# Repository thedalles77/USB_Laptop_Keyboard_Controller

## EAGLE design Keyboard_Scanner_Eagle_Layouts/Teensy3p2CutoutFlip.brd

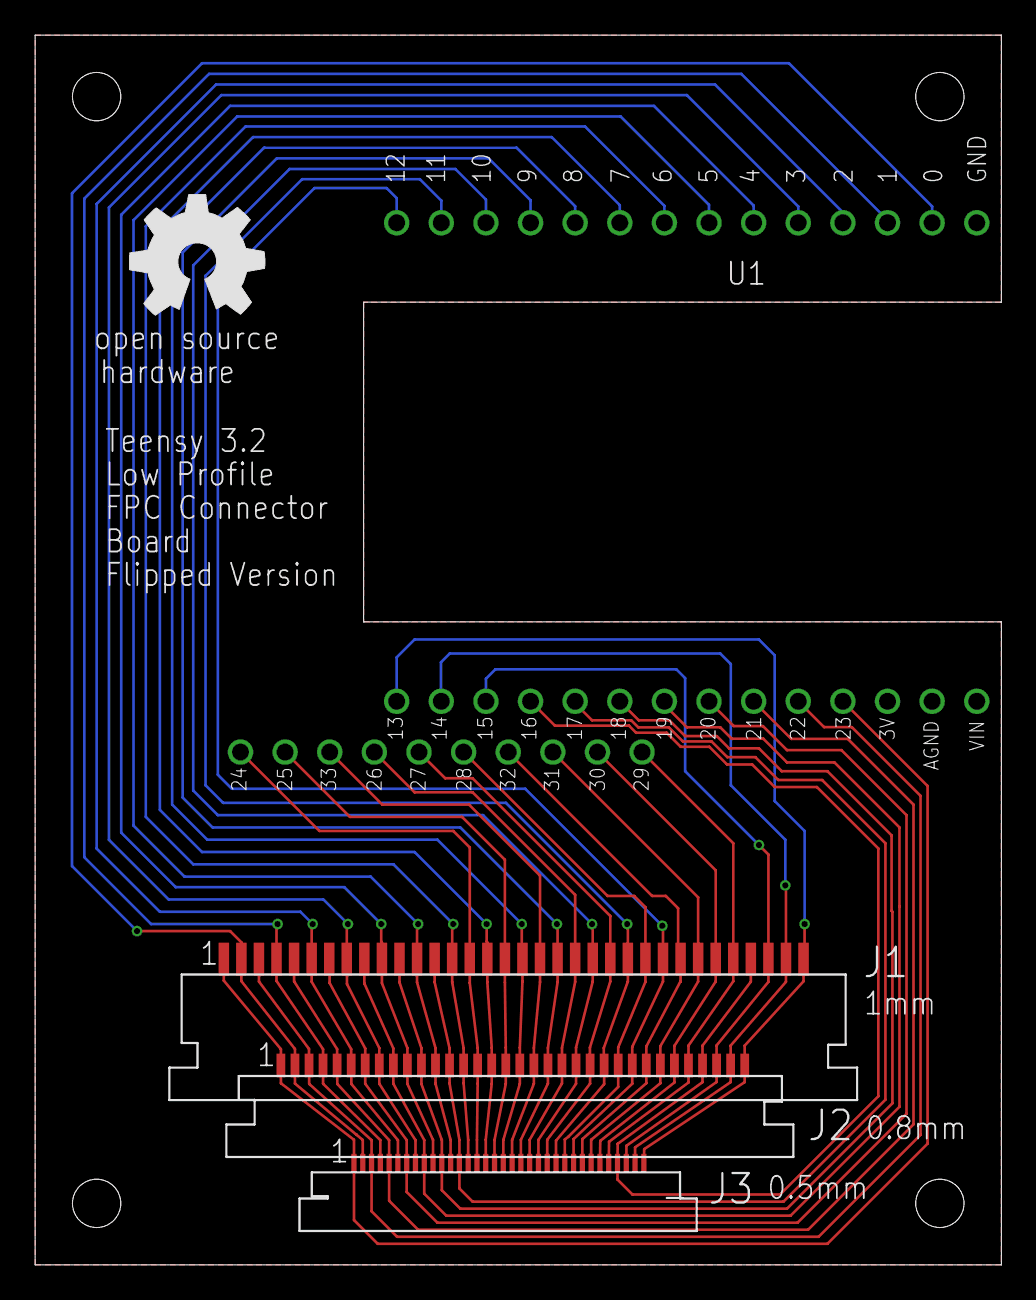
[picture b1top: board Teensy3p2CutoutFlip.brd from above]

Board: 2 copper layers, 55.0 x 70.0 mm, 5 parts (0 on the bottom side), 34 nets.

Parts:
J1: 1mm; FPC34
J2: 0.8mm; FPC34_P8MM
J3: 0.5mm; FPC34_P5MM
U1: Teensy 3.2; TEENSY3P2CUTOUT
U$1: OSHW_8MM

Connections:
0: J1.2, J2.2, J3.2, U1.0
1: J1.4, J2.4, J3.4, U1.1
2: J1.6, J2.6, J3.6, U1.2
3: J1.8, J2.8, J3.8, U1.3
4: J1.10, J2.10, J3.10, U1.4
5: J1.12, J2.12, J3.12, U1.5
6: J1.14, J2.14, J3.14, U1.6
7: J1.16, J2.16, J3.16, U1.7
8: J1.18, J2.18, J3.18, U1.8
9: J1.20, J2.20, J3.20, U1.9
10: J1.22, J2.22, J3.22, U1.10
11: J1.24, J2.24, J3.24, U1.11
12: J1.26, J2.26, J3.26, U1.12
13: J1.34, J2.34, J3.34, U1.13
14: J1.33, J2.33, J3.33, U1.14
15: J1.32, J2.32, J3.32, U1.15
16: J1.31, J2.31, J3.31, U1.16
17: J1.13, J2.13, J3.13, U1.17
18: J1.11, J2.11, J3.11, U1.18
19: J1.9, J2.9, J3.9, U1.19
20: J1.7, J2.7, J3.7, U1.20
21: J1.5, J2.5, J3.5, U1.21
22: J1.3, J2.3, J3.3, U1.22
23: J1.1, J2.1, J3.1, U1.23
24: J1.15, J2.15, J3.15, U1.24
25: J1.17, J2.17, J3.17, U1.25
26: J1.21, J2.21, J3.21, U1.26
27: J1.23, J2.23, J3.23, U1.27
28: J1.25, J2.25, J3.25, U1.28
29: J1.30, J2.30, J3.30, U1.29
30: J1.29, J2.29, J3.29, U1.30
31: J1.28, J2.28, J3.28, U1.31
32: J1.27, J2.27, J3.27, U1.32
33: J1.19, J2.19, J3.19, U1.33

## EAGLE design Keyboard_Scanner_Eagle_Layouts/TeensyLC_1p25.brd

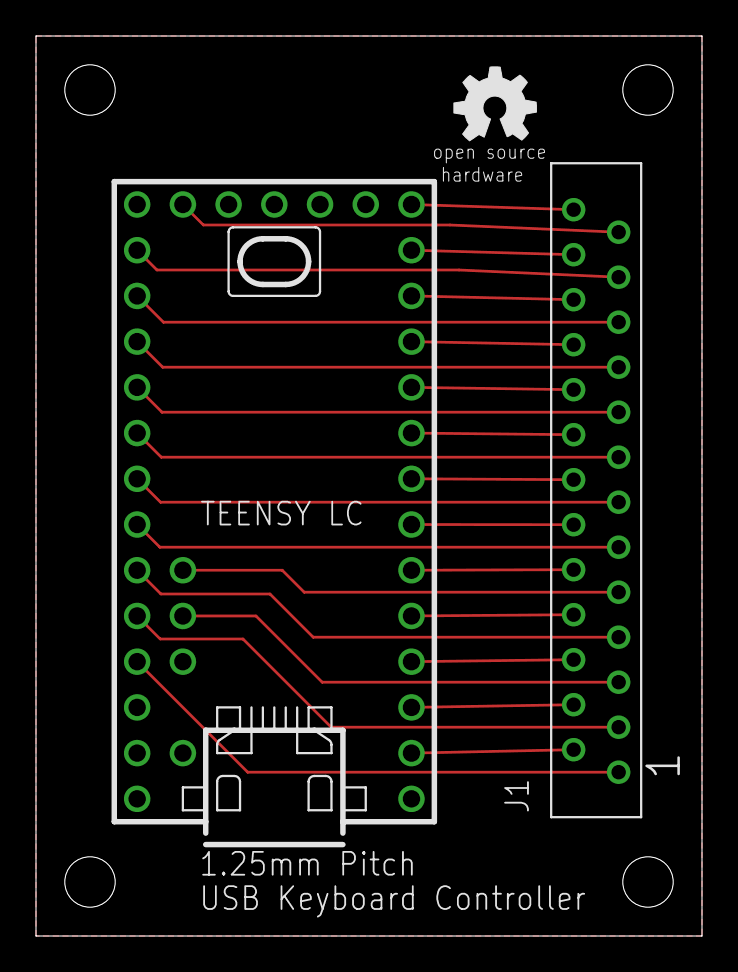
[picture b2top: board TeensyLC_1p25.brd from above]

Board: 2 copper layers, 37.0 x 50.0 mm, 3 parts (0 on the bottom side), 27 nets.

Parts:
J1: 1.25MM DIP FPC; CONN_1P25
U$1: TEENSY_LC
U$2: OSHW_5MM

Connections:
GND: U$1.GND1, U$1.GND2, U$1.GND3
IO_0: J1.P$2, U$1.0
IO_1: J1.P$4, U$1.1
IO_2: J1.P$6, U$1.2
IO_3: J1.P$8, U$1.3
IO_4: J1.P$10, U$1.4
IO_5: J1.P$12, U$1.5
IO_6: J1.P$14, U$1.6
IO_7: J1.P$16, U$1.7
IO_8: J1.P$18, U$1.8
IO_9: J1.P$20, U$1.9
IO_10: J1.P$22, U$1.10
IO_11: J1.P$24, U$1.11
IO_12: J1.P$26, U$1.12
IO_14: J1.P$23, U$1.14
IO_15: J1.P$21, U$1.15
IO_16: J1.P$19, U$1.16
IO_17: J1.P$17, U$1.17
IO_18: J1.P$15, U$1.18
IO_19: J1.P$13, U$1.19
IO_20: J1.P$11, U$1.20
IO_21: J1.P$7, U$1.21
IO_22: J1.P$3, U$1.22
IO_23: J1.P$1, U$1.23
IO_24: J1.P$5, U$1.24
IO_25: J1.P$9, U$1.25
IO_26: J1.P$25, U$1.26

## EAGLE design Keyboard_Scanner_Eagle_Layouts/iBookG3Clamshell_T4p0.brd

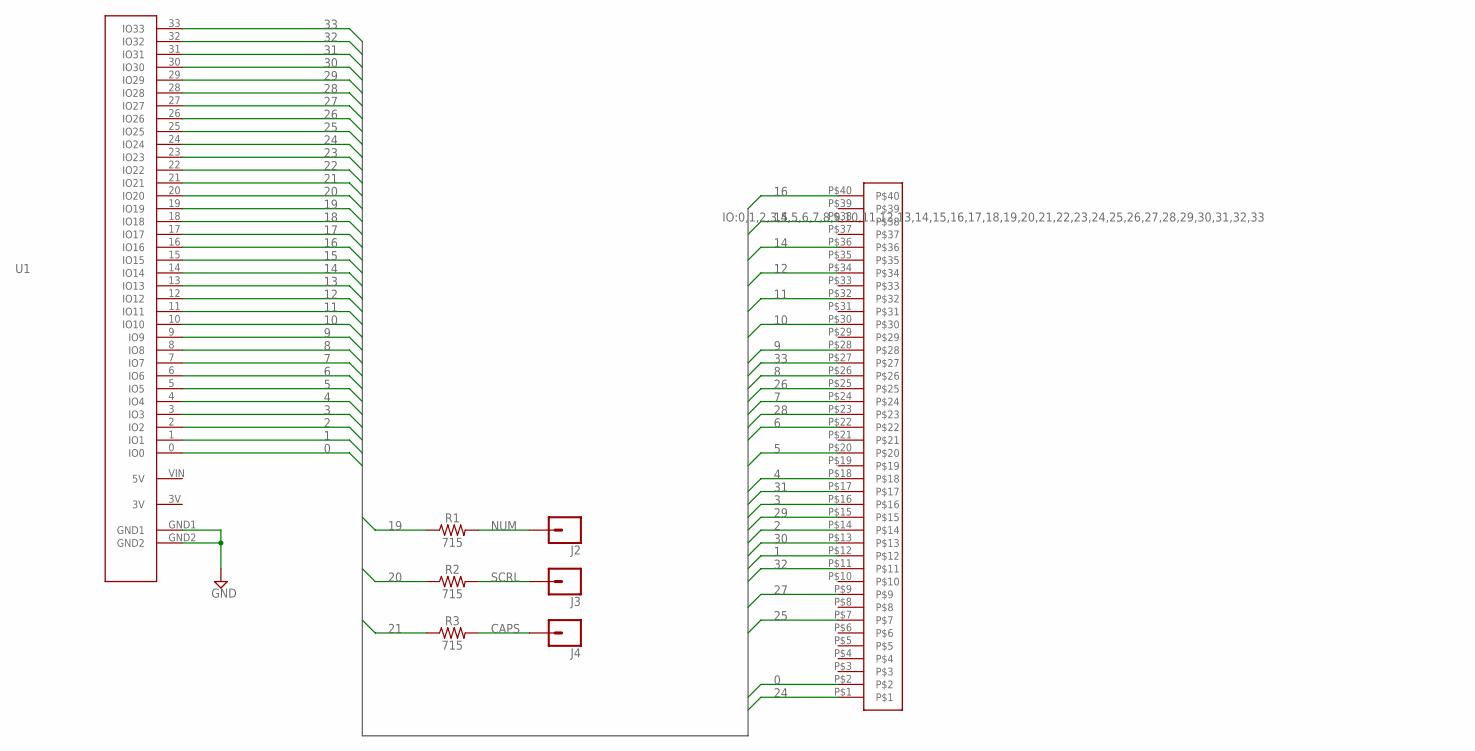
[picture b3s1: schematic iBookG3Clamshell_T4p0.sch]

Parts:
J1: HDR127MET40FGVSMDR
J2, J3, J4: CONN_01PTH_NO_SILK_YES_STOP; 1X01_NO_SILK
R1, R2, R3: 715; 0603
U1: TEENSY4P0_CUTOUT

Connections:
0: J1.P$2, U1.0 (IO0)
1: J1.P$12, U1.1 (IO1)
2: J1.P$14, U1.2 (IO2)
3: J1.P$16, U1.3 (IO3)
4: J1.P$18, U1.4 (IO4)
5: J1.P$20, U1.5 (IO5)
6: J1.P$22, U1.6 (IO6)
7: J1.P$24, U1.7 (IO7)
8: J1.P$26, U1.8 (IO8)
9: J1.P$28, U1.9 (IO9)
10: J1.P$30, U1.10 (IO10)
11: J1.P$32, U1.11 (IO11)
12: J1.P$34, U1.12 (IO12)
13: U1.13 (IO13)
14: J1.P$36, U1.14 (IO14)
15: J1.P$38, U1.15 (IO15)
16: J1.P$40, U1.16 (IO16)
17: U1.17 (IO17)
18: U1.18 (IO18)
19: R1.1, U1.19 (IO19)
20: R2.1, U1.20 (IO20)
21: R3.1, U1.21 (IO21)
22: U1.22 (IO22)
23: U1.23 (IO23)
24: J1.P$1, U1.24 (IO24)
25: J1.P$7, U1.25 (IO25)
26: J1.P$25, U1.26 (IO26)
27: J1.P$9, U1.27 (IO27)
28: J1.P$23, U1.28 (IO28)
29: J1.P$15, U1.29 (IO29)
30: J1.P$13, U1.30 (IO30)
31: J1.P$17, U1.31 (IO31)
32: J1.P$11, U1.32 (IO32)
33: J1.P$27, U1.33 (IO33)
CAPS: J4.1, R3.2
GND: U1.GND1, U1.GND2
NUM: J2.1, R1.2
SCRL: J3.1, R2.2

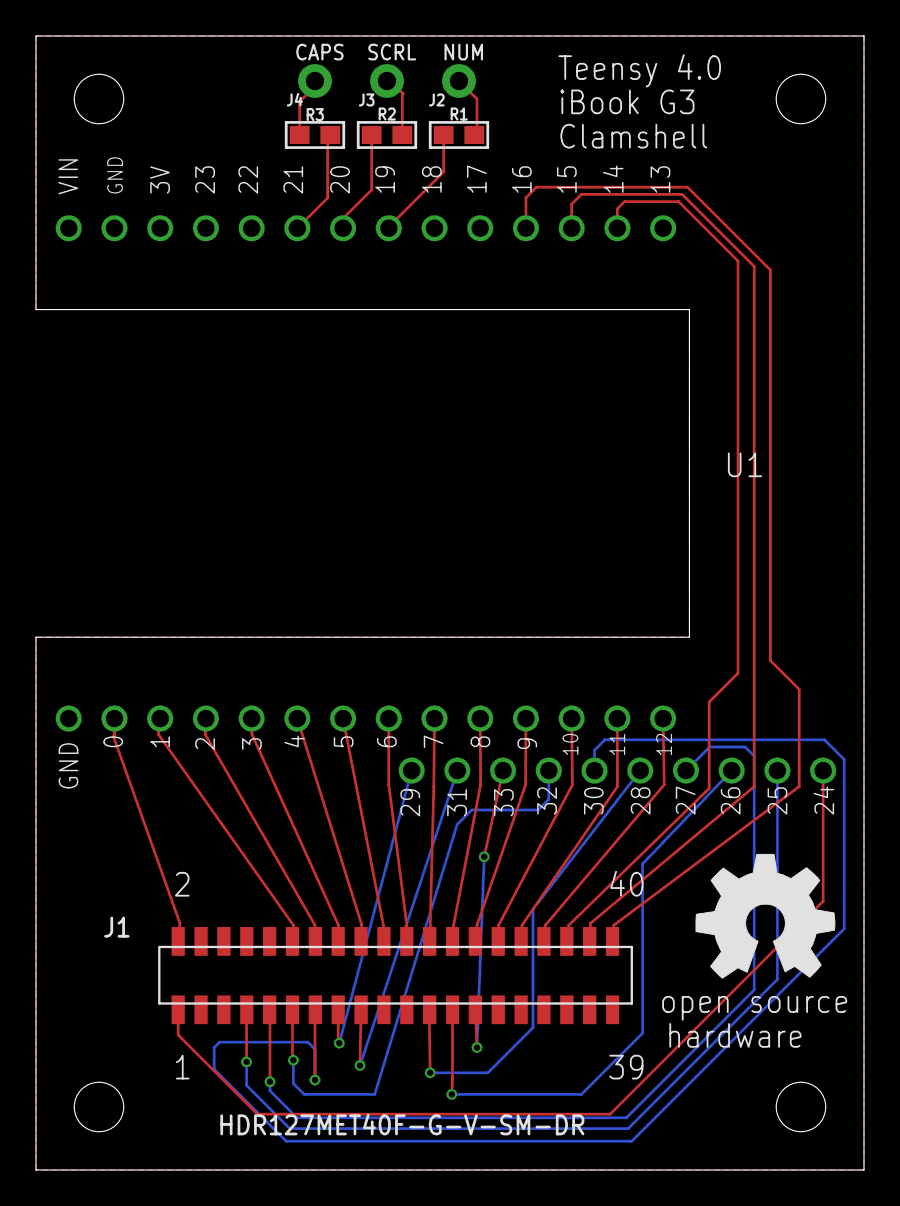
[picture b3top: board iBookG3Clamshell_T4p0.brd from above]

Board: 2 copper layers, 46.0 x 63.0 mm, 9 parts (0 on the bottom side), 33 nets.

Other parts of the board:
U$1: OSHW_8MM

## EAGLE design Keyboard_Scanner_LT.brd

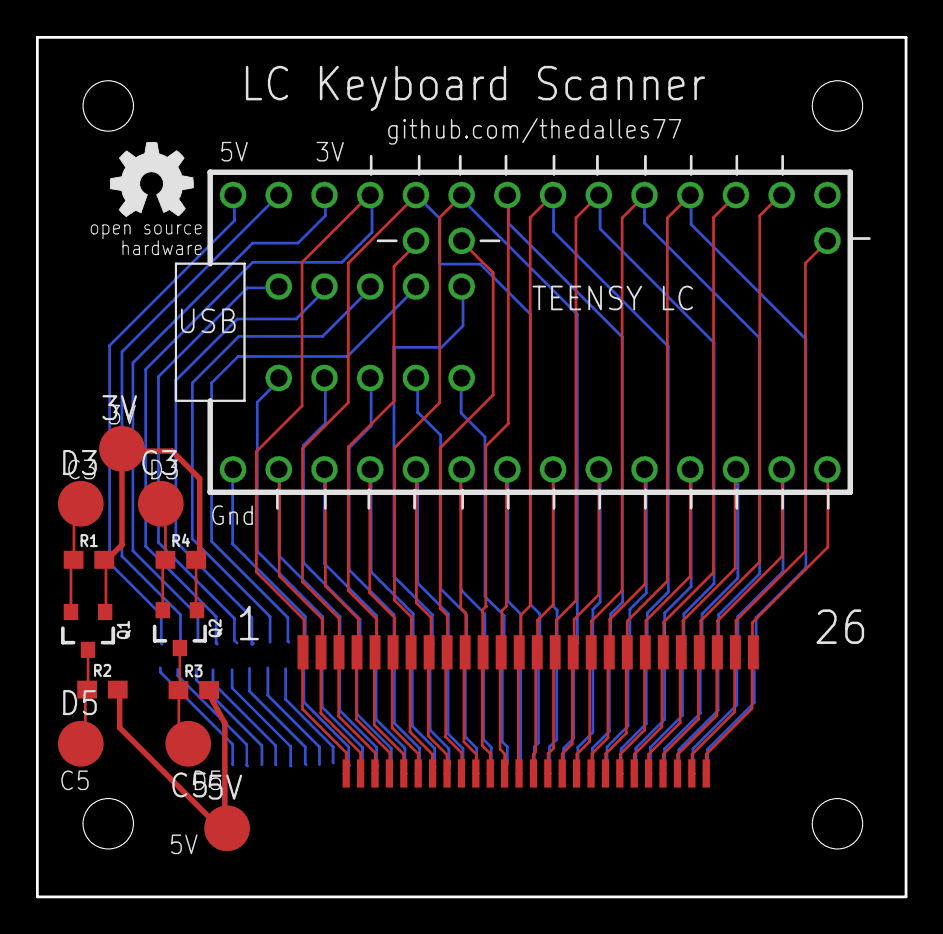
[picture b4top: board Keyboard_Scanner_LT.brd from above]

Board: 2 copper layers, 48.3 x 47.8 mm, 16 parts (0 on the bottom side), 4 nets.

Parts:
3V, 5V: B2,54
C3, C5: B2,54
D3, D5: B2,54
E$1: TEENSY_COMBO
E$2: FPC_DUAL
E$3: FPC_DUAL_FRONT
E$4: OSHW_5MM
Q1, Q2: 220mA/50V/3.5Ω; SOT23-3
R1, R2, R3, R4: 10k; 0603

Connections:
CLK: Q1.2, R1.1
DATA: Q2.2, R4.1
TP_CLK: Q1.3, R2.1
TP_DATA: Q2.3, R3.1

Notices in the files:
parts and their libraries:
SparkFun-Connectors: Licensing: Creative Commons ShareAlike 4.0 International - https://creativecommons.org/licenses/by-sa/4.0
